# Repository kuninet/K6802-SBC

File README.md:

# MC6802 MPUを使ったシングルボードコンピューター

## REV1はシリアルクロック回路にバグがあります!!
## REV2で修正

## 概要
* MC6802 MPUを使ったシングルボードコンピューターです。
  * MC6850 ACIA経由でシリアルターミナル(TeraTermなど)とつながります。(SBC6800と互換)
  * 64kBのメモリー領域にRAMをわりあてるため128kB SRAMを使用しています。(半分の64kBは無駄にしています)
    * 半田ジャンパによりメモリー領域を調整可能です。(外部ボードのRAM用にディセーブル or ROM領域へ割り当て)
  * ROMは32kBタイプですが、ジャンパで2つの領域に分けて使用できます。
* SBC6800のソフトを使えることを目指しました。

## 回路図

## 部品表
[部品表](KiCad/K6802-SBC.csv)

## ブラウザで回路図などを確認
* Kicadcanvas
  * https://kicanvas.org/?github=https%3A%2F%2Fgithub.com%2Fkuninet%2FK6802-SBC%2Ftree%2Fmain%2FKiCad

## 参考
* 以下の回路を参考にさせていただきました。ありがとうございます。
  * [SBC6800 ルーズキット (電脳伝説さん)](https://vintagechips.wordpress.com/2017/12/05/sbc6800%E3%83%AB%E3%83%BC%E3%82%BA%E3%82%AD%E3%83%83%E3%83%88/)
  * [SBC-IO Rev02 (Tomi9さん)](https://sbc738827564.wordpress.com/2018/08/11/sbc-io-rev02/)
  * [SBC8080 SUBルーズキット (電脳伝説さん)](https://vintagechips.wordpress.com/2018/06/23/sbc8080-sub%E3%83%AB%E3%83%BC%E3%82%BA%E3%82%AD%E3%83%83%E3%83%88/)
  * [SBC6802 (ryu10さん)](https://github.com/ryu10/sbc6802)

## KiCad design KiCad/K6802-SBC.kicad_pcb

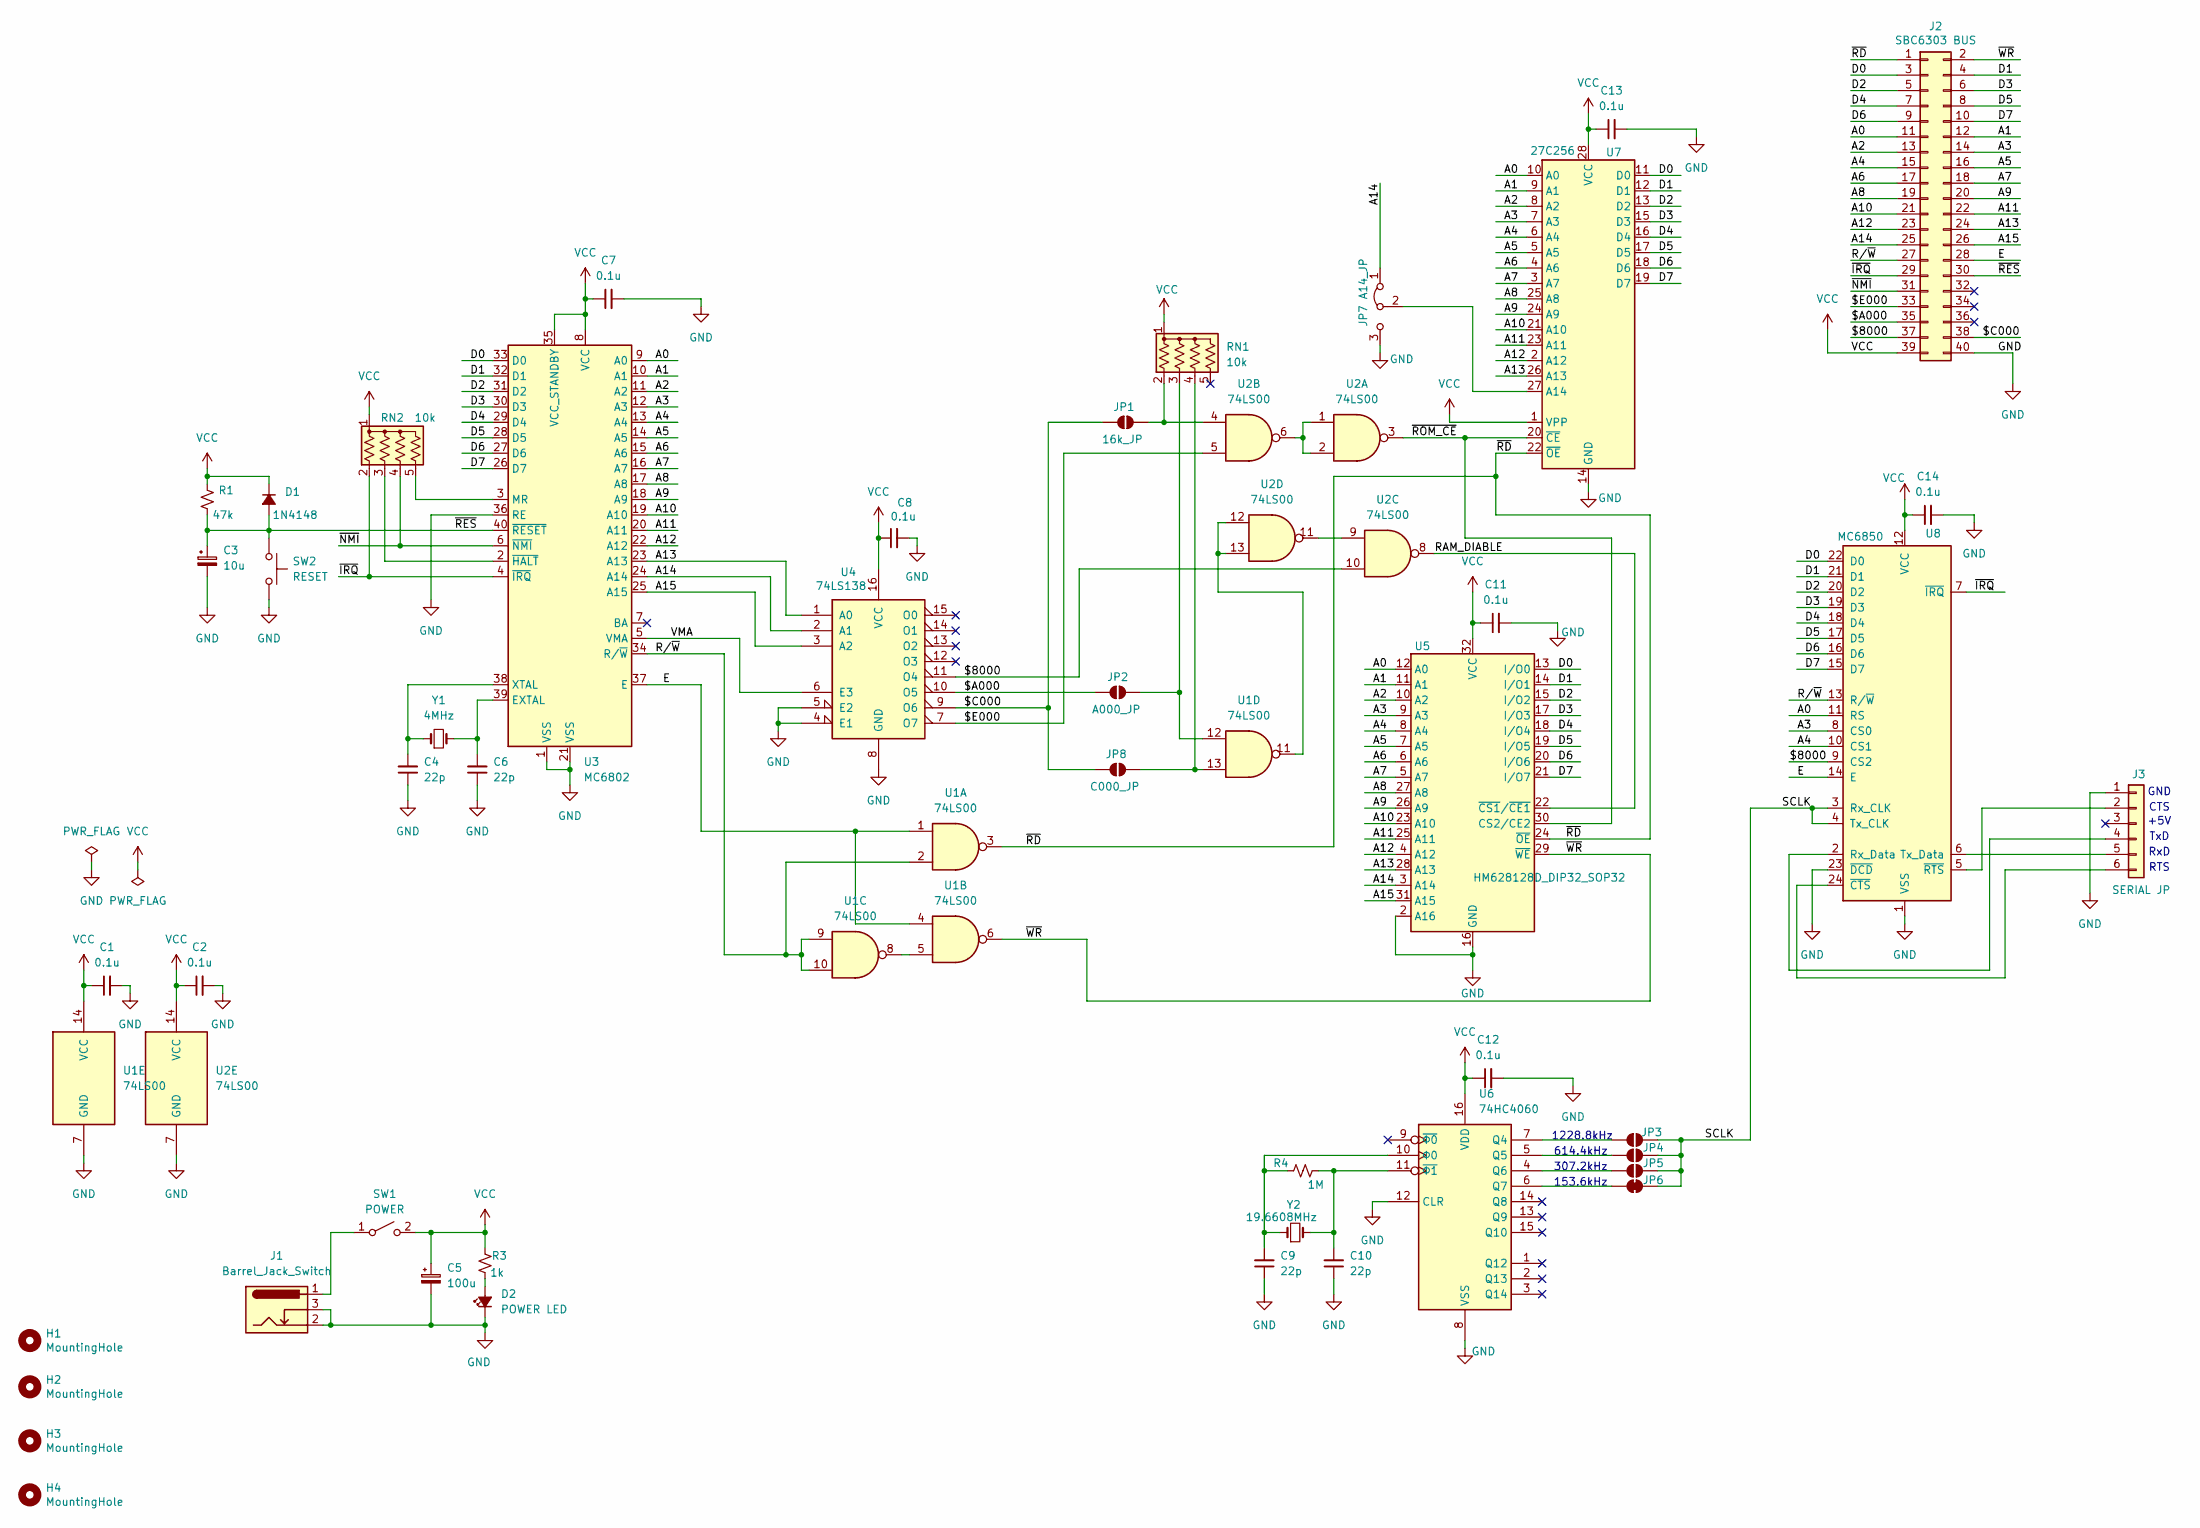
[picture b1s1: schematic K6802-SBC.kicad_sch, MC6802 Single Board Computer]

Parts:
C1, C2, C7, C8, C11, C12, C13, C14: 0.1u; C_Disc_D3.0mm_W2.0mm_P2.50mm
C3: 10u; CP_Radial_D5.0mm_P2.50mm
C4, C6, C9, C10: 22p; C_Disc_D3.0mm_W2.0mm_P2.50mm
C5: 100u; CP_Radial_D5.0mm_P2.50mm
D1: 1N4148; D_A-405_P10.16mm_Horizontal
D2: POWER LED; LED_D3.0mm
H1, H2, H3, H4: MountingHole; MountingHole_3.2mm_M3
J1: Barrel_Jack_Switch; BarrelJack_Horizontal
J2: SBC6303 BUS; PinHeader_2x20_P2.54mm_Horizontal
J3: SERIAL JP; PinHeader_1x06_P2.54mm_Horizontal
JP1: 16k_JP; SolderJumper-2_P1.3mm_Open_RoundedPad1.0x1.5mm
JP2: A000_JP; SolderJumper-2_P1.3mm_Open_RoundedPad1.0x1.5mm
JP3, JP4, JP5: SolderJumper-2_P1.3mm_Open_RoundedPad1.0x1.5mm
JP6: SolderJumper_2_Bridged; SolderJumper-2_P1.3mm_Bridged_RoundedPad1.0x1.5mm
JP7: A14_JP; PinHeader_1x03_P2.54mm_Vertical
JP8: C000_JP; SolderJumper-2_P1.3mm_Open_RoundedPad1.0x1.5mm
R1: 47k; R_Axial_DIN0207_L6.3mm_D2.5mm_P10.16mm_Horizontal
R3: 1k; R_Axial_DIN0207_L6.3mm_D2.5mm_P10.16mm_Horizontal
R4: 1M; R_Axial_DIN0207_L6.3mm_D2.5mm_P10.16mm_Horizontal
RN1, RN2: 10k; R_Array_SIP5
SW1: POWER; PinHeader_1x03_P2.54mm_Vertical
SW2: RESET; SW_PUSH_6mm
U1, U2: 74LS00; DIP-14_W7.62mm_Socket
U3: MC6802; DIP-40_W15.24mm_Socket
U4: 74LS138; DIP-16_W7.62mm_Socket
U5: HM628128D_DIP32_SOP32; DIP-32_W15.24mm_Socket
U6: 74HC4060; DIP-16_W7.62mm_Socket
U7: 27C256; DIP-28_W15.24mm_Socket
U8: MC6850; DIP-24_W15.24mm_Socket
Y1: 4MHz; Crystal_HC49-U_Vertical
Y2: 19.6608MHz; Crystal_HC49-U_Vertical

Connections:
/$8000: J2.37, U2.10, U4.11 (O4), U8.9 (CS2)
/$A000: J2.35, JP2.1 (A), U4.10 (O5)
/$C000: J2.38, JP1.1 (A), JP8.1 (A), U4.9 (O6)
/$E000: J2.33, U2.5, U4.7 (O7)
/A0: J2.11, U3.9 (A0), U5.12 (A0), U7.10 (A0), U8.11 (RS)
/A1: J2.12, U3.10 (A1), U5.11 (A1), U7.9 (A1)
/A2: J2.13, U3.11 (A2), U5.10 (A2), U7.8 (A2)
/A3: J2.14, U3.12 (A3), U5.9 (A3), U7.7 (A3), U8.8 (CS0)
/A4: J2.15, U3.13 (A4), U5.8 (A4), U7.6 (A4), U8.10 (CS1)
/A5: J2.16, U3.14 (A5), U5.7 (A5), U7.5 (A5)
/A6: J2.17, U3.15 (A6), U5.6 (A6), U7.4 (A6)
/A7: J2.18, U3.16 (A7), U5.5 (A7), U7.3 (A7)
/A8: J2.19, U3.17 (A8), U5.27 (A8), U7.25 (A8)
/A9: J2.20, U3.18 (A9), U5.26 (A9), U7.24 (A9)
/A10: J2.21, U3.19 (A10), U5.23 (A10), U7.21 (A10)
/A11: J2.22, U3.20 (A11), U5.25 (A11), U7.23 (A11)
/A12: J2.23, U3.22 (A12), U5.4 (A12), U7.2 (A12)
/A13: J2.24, U3.23 (A13), U4.1 (A0), U5.28 (A13), U7.26 (A13)
/A14: J2.25, JP7.1 (A), U3.24 (A14), U4.2 (A1), U5.3 (A14)
/A15: J2.26, U3.25 (A15), U4.3 (A2), U5.31 (A15)
/D0: J2.3, U3.33 (D0), U5.13 (I/O0), U7.11 (D0), U8.22 (D0)
/D1: J2.4, U3.32 (D1), U5.14 (I/O1), U7.12 (D1), U8.21 (D1)
/D2: J2.5, U3.31 (D2), U5.15 (I/O2), U7.13 (D2), U8.20 (D2)
/D3: J2.6, U3.30 (D3), U5.17 (I/O3), U7.15 (D3), U8.19 (D3)
/D4: J2.7, U3.29 (D4), U5.18 (I/O4), U7.16 (D4), U8.18 (D4)
/D5: J2.8, U3.28 (D5), U5.19 (I/O5), U7.17 (D5), U8.17 (D5)
/D6: J2.9, U3.27 (D6), U5.20 (I/O6), U7.18 (D6), U8.16 (D6)
/D7: J2.10, U3.26 (D7), U5.21 (I/O7), U7.19 (D7), U8.15 (D7)
/E: J2.28, U1.1, U1.4, U3.37 (E), U8.14 (E)
/RAM_DIABLE: U2.8, U5.22 (~CS1/~CE1)
/R/~W: J2.27, U1.2, U1.9, U1.10, U3.34 (R/~W), U8.13 (R/~W)
/SCLK: JP3.2 (B), JP4.2 (B), JP5.2 (B), JP6.2 (B), U8.3 (Rx_CLK), U8.4 (Tx_CLK)
/VMA: U3.5 (VMA), U4.6 (E3)
/~IRQ: J2.29, RN2.2 (R1), U3.4 (~IRQ), U8.7 (~IRQ)
/~NMI: J2.31, RN2.4 (R3), U3.6 (~NMI)
/~RD: J2.1, U1.3, U5.24 (~OE), U7.22 (~OE)
/~RES: C3.1, D1.2 (A), J2.30, R1.2, SW2.1, U3.40 (~RESET)
/~ROM_CE: U2.3, U5.30 (CS2/CE2), U7.20 (~CE)
/~WR: J2.2, U1.6, U5.29 (~WE)
GND: C1.2, C2.2, C3.2, C4.1, C5.2, C6.1, C7.2, C8.2, C9.1, C10.1, C11.2, C12.2, C13.2, C14.2, D2.1 (K), J1.2, J1.3, J2.40, J3.1, JP7.3 (B), SW2.2, U1.7 (GND), U2.7 (GND), U3.1 (VSS), U3.21 (VSS), U3.36 (RE), U4.4 (E1), U4.5 (E2), U4.8 (GND), U5.2 (A16), U5.16 (GND), U6.8 (VSS), U6.12 (CLR), U7.14 (GND), U8.1 (VSS), U8.23 (~DCD)
unnamed: D2.2 (A), R3.2
unnamed: J3.2, U8.5 (~RTS)
unnamed: J3.4, U8.2 (Rx_Data)
unnamed: J3.5, U8.6 (Tx_Data)
unnamed: J3.6, U8.24 (~CTS)
unnamed: JP1.2 (B), RN1.2 (R1), U2.4
unnamed: JP2.2 (B), RN1.3 (R2), U1.12
unnamed: JP3.1 (A), U6.7 (Q4)
unnamed: JP4.1 (A), U6.5 (Q5)
unnamed: JP5.1 (A), U6.4 (Q6)
unnamed: JP6.1 (A), U6.6 (Q7)
unnamed: JP7.2 (C), U7.27 (A14)
unnamed: JP8.2 (B), RN1.4 (R3), U1.13
unnamed: RN2.3 (R2), U3.2 (~HALT)
unnamed: RN2.5 (R4), U3.3 (MR)
unnamed: J1.1, SW1.1 (A)
unnamed: U1.5, U1.8
unnamed: U1.11, U2.12, U2.13
unnamed: U2.1, U2.2, U2.6
unnamed: U2.9, U2.11
unnamed: C6.2, U3.39 (EXTAL), Y1.2
unnamed: C4.2, U3.38 (XTAL), Y1.1
unnamed: C10.2, R4.2, U6.11 (~Φ1), Y2.2
unnamed: C9.2, R4.1, U6.10 (Φ0), Y2.1
VCC: C1.1, C2.1, C5.1, C7.1, C8.1, C11.1, C12.1, C13.1, C14.1, D1.1 (K), J2.39, R1.1, R3.1, RN1.1 (common), RN2.1 (common), SW1.2 (B), U1.14 (VCC), U2.14 (VCC), U3.8 (VCC), U3.35 (VCC_STANDBY), U4.16 (VCC), U5.32 (VCC), U6.16 (VDD), U7.1 (VPP), U7.28 (VCC), U8.12 (VCC)

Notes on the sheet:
GND
153.6kHz
CTS
+5V
RxD
307.2kHz
614.4kHz
1228.8kHz
RTS
TxD

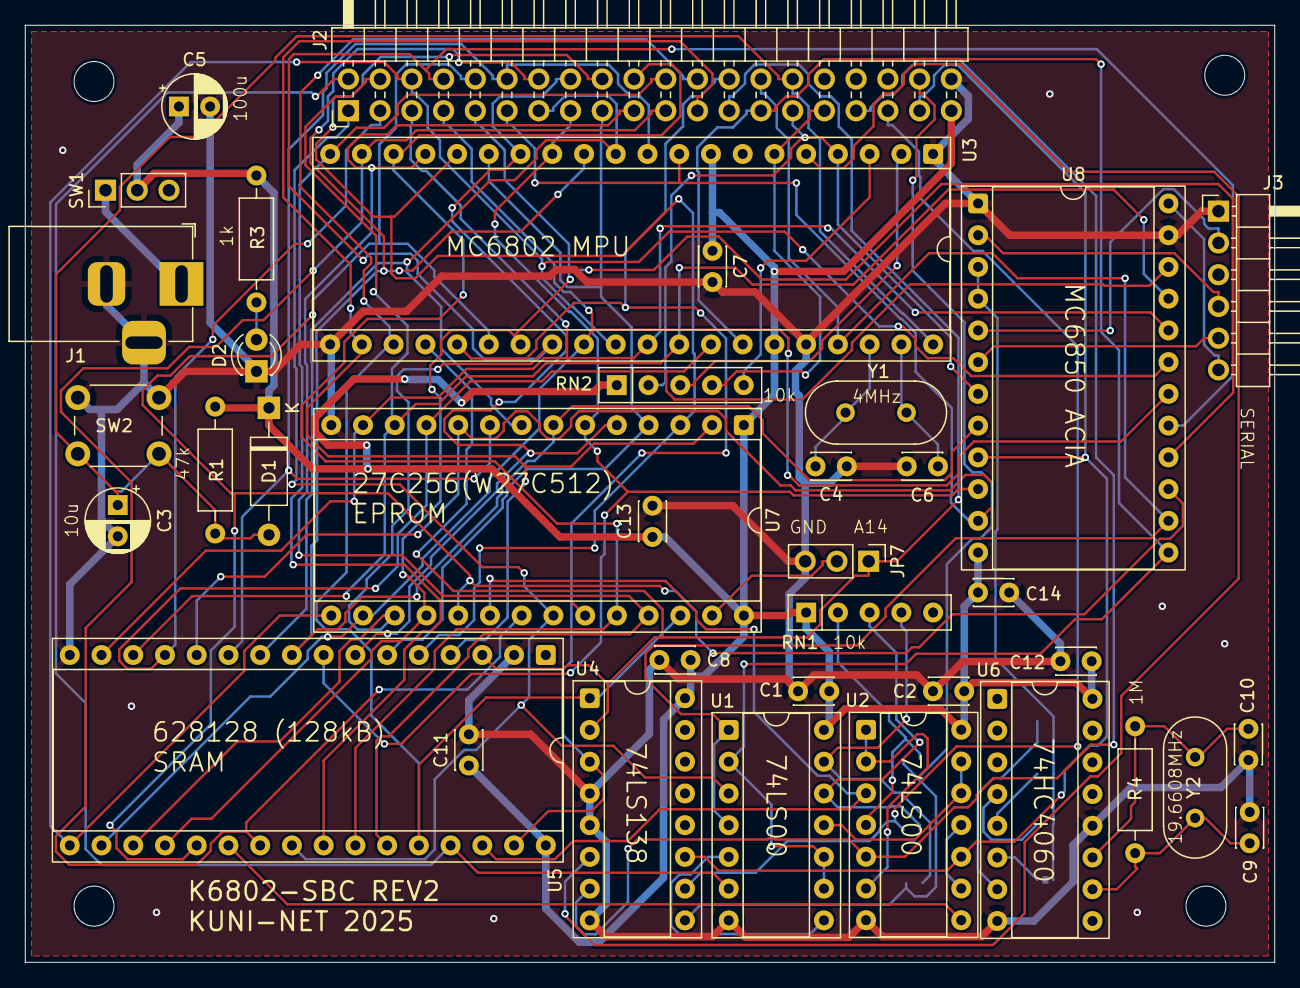
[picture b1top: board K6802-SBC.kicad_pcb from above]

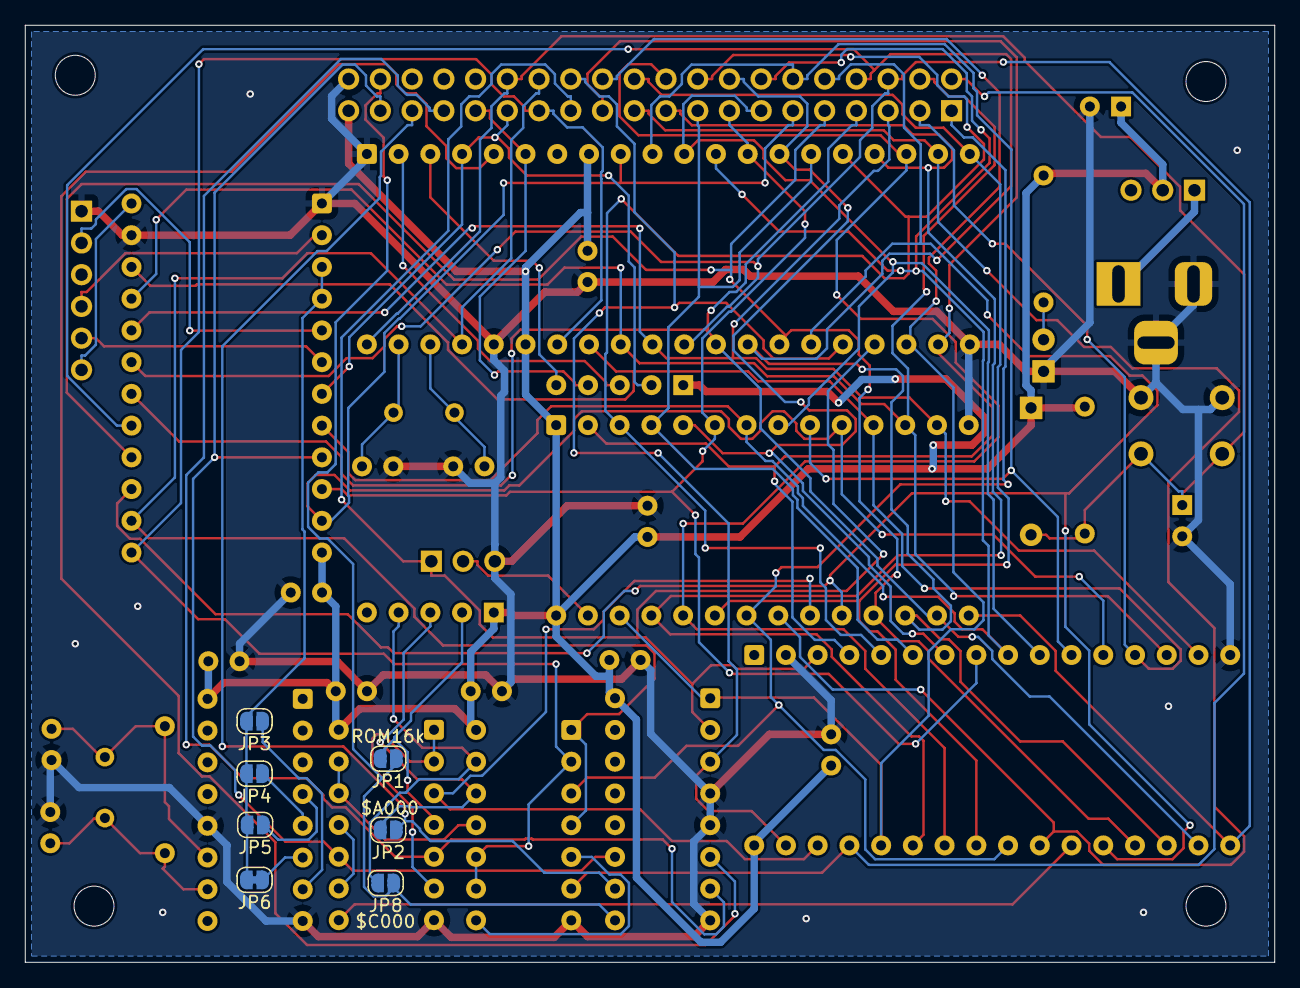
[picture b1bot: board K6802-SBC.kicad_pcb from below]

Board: 2 copper layers, 100.0 x 75.0 mm, 48 parts (7 on the bottom side), 65 nets.

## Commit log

2025-03-01 init commit
2025-03-01 Create LICENSE
2025-03-02 プリントパターン作成、ガーバーデータ出力
2025-03-11 シリアルクロック間違い修正(回路図だけ)
2025-03-18 メモリーマップ図追加
2025-03-20 ROM16k-8k図作成
2025-03-20 .gitignore変更
2025-03-20 $C000無効かジャンパ追加 REV2ガーバー出力
